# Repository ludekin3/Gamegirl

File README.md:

# Gamegirl

The most portable way to play LÖVE, PICO-8, Scratch or your favorite emulated games. Powered by RetroArch!

# Table of Contents

* [Description](#description)
* [Components](#components)
* [Build your own!](#build-your-own)
* [Setup](#setup)
* [Team](#team)
* [License](#license)

# Description
We develop a very small, affordable and portable gaming console with a 320x240 display at 120 FPS run by a Raspberry Pi Zero.
Gamegirl runs on the Lakka distribution powered by RetroArch because of its speed, fast power-on, instant power-off and its potential to run many retro and hipster-retro games (LÖVE, PICO-8, Scratch and emulators).

[**Join us on our Discord Chat Channel!**](https://discord.gg/TZ7MZEu)

<p align="center">
    
</p>

**Project Goals:**
* Hardware accelerated display
* Custom software (Lakka / RetroArch)
* High quality case and buttons
* Small form factor

# Components
* 1 x Gamegirl custom PCB (audio, power, etc.)
* 1 × Raspberry Pi Zero
* 1 × 2.4" TFT display 320x240 (RGB 565 @ 120 FPS)
* 10 × soft rubber dome buttons
* 2 x metal dome buttons
* 1 × 15-16mm speaker
* 1 × 800+ mAh battery

# Build your own!

## Prototype v0.2 (_released_)
**v0.2** is the current development platform with multiple working prototypes in the field. It works but it's not perfect, yet!

### Gamegirl v0.2 - Schematic
* [Gamegirl_v0.2_Schematic.pdf](./Electronics%20v0.2/Gamegirl_v0.2_Schematic.pdf)

### Gamegirl v0.2 - Bill Of Materials (BOM)
* [Octopart - Gamegirl v0.2 BOM](https://octopart.com/bom-tool/0X5BikOH)

#### Minimal assembly variant
In this assembly variant you will get a working prototype without battery/charging and audio functionality. You can use it only while the Raspberry Pi Zero is connected to a USB power supply!
* [Gamegirl v0.2 BOM - minimal assembly variant](./Electronics%20v0.2/Gamegirl_v0.2_BOM_minimal.pdf)

#### Full assembly variant
This assembly variant requires some circuit modifications to get audio output!
* [Gamegirl v0.2 BOM - full assembly variant](./Electronics%20v0.2/Gamegirl_v0.2_BOM.pdf)

### Gamegirl Case v0.2
A 3D printable case design is currently in work.

## Prototype v0.2.1 (Awaiting Prototype board)
**v0.2.1** incorporates multiple improvements and fixes over v0.2. If you do not have a v0.2, you should wait for this!

**Improvements over v0.2:**
* Friendlier hand solderable layout (All component footprints have been expanded for soldering without a heatgun)
* Fixed mono audio circuit (better pre and post filtering)
* Fixed backlight function
* Button placement and labeling to reflect standard Nintendo layout
* MCP23S17 GPIO Expander replaced Charlieplexed buttons
* Labeled most 
* Ability to add common inexpensive WiFi adpater directly to the board (depreciated due to Zero W)
* Replaced battery charger and 5v booster ICs with a 3-in-1 IC, ETA9740
** Rpi Zero will run directly from battery (Rpi stability has been tested down to 3.0V)
** Increased charging current from 500mA to 2A or 3A
** 5V Boost will operate in USB-OTG mode for accessories
* Added dedicated charging micro USB port (Rpi ports will be covered)
* Added multiple power decoupling capacitors for better power filtering
* Added Safe Soft-Shutdown circuit
* Replaced latching switch with momentary switch
* (Optional) Low Battery shutdown
* (Optional) Low Noise LDO for audio amp (Must cut 3.3v trace when using)

### Gamegirl v0.2.1 - Bill Of Materials (BOM)
[BOM](./Electronics%20v0.2.1/Gamegirl_v0.2.1_BOM.csv)

### Gamegirl Case v0.2.1
(work in progress)

# Setup
## Install the latest Lakka image on an SD Card

**Gamegirl Raspberry Pi Zero images:**
* [Nightly Builds](http://sources.lakka.tv/nightly/Gamegirl.arm-8.0/)
* [Build r21684 (November 29, 2016)](http://static.kivutar.me/Lakka-Gamegirl.arm-devel-20161129161645-r21684-g895e996.img.gz)
* [Build r21570 (August 23, 2016)](http://static.kivutar.me/Lakka-Gamegirl.arm-devel-20160823060147-r21570-g1cacbe2.img.gz)

**Instructions:**
* [How to write a image to an SD card on Windows & Mac OS](http://trendblog.net/install-raspbian-sd-card-os-x-windows/)

## First boot
As of nightly build 20170110005640-r25097, the system will take longer to boot as it is expanding the SD card partition and running other first boot operations. Subsequent boots will be faster.

## Installing your games
How-to [on lakka.tv](http://www.lakka.tv/get/linux/rpi/install/first-boot/games/)

# Team
|  |  |  
| --- | --- | --- |
| [David Perrenoud](https://github.com/davidperrenoud) | [Jean-André Santoni](http://www.kivutar.me/) - [Github](https://github.com/Kivutar) | [Rodney Yates](https://github.com/zybeon)

- [Jean-André] from France is the software guy of this project. He is the main Lakka developer and a top 5 RetroArch contributor.
- [David] from Switzerland is the hardware guy.
- [Rodney] from US is the PCB designer.

## Contributing
[Join us on our Discord Chat Channel!](https://discord.gg/TZ7MZEu)

### Project Task Tracker
[Trello page](https://trello.com/b/wslfYlVv/gamegirl)

#License

All hardware is covered under [OSHW](https://www.oshwa.org/definition/).

All software is covered under [GNU-GPL 3.0](https://opensource.org/licenses/GPL-3.0).

Permission is hereby granted, free of charge, to any person obtaining a copy of this software and associated documentation files (the "Software"), to deal in the Software without restriction, including without limitation the rights to use, copy, modify, merge, publish, distribute, sublicense, and/or sell copies of the Software, and to permit persons to whom the Software is furnished to do so, subject to the following conditions:  The above copyright notice and this permission notice shall be included in all copies or substantial portions of the Software. THE SOFTWARE IS PROVIDED "AS IS", WITHOUT WARRANTY OF ANY KIND, EXPRESS OR IMPLIED, INCLUDING BUT NOT LIMITED TO THE WARRANTIES OF MERCHANTABILITY, FITNESS FOR A PARTICULAR PURPOSE AND NONINFRINGEMENT. IN NO EVENT SHALL THE AUTHORS OR COPYRIGHT HOLDERS BE LIABLE FOR ANY CLAIM, DAMAGES OR OTHER LIABILITY, WHETHER IN AN ACTION OF CONTRACT, TORT OR OTHERWISE, ARISING FROM, OUT OF OR IN CONNECTION WITH THE SOFTWARE OR THE USE OR OTHER DEALINGS IN THE SOFTWARE."

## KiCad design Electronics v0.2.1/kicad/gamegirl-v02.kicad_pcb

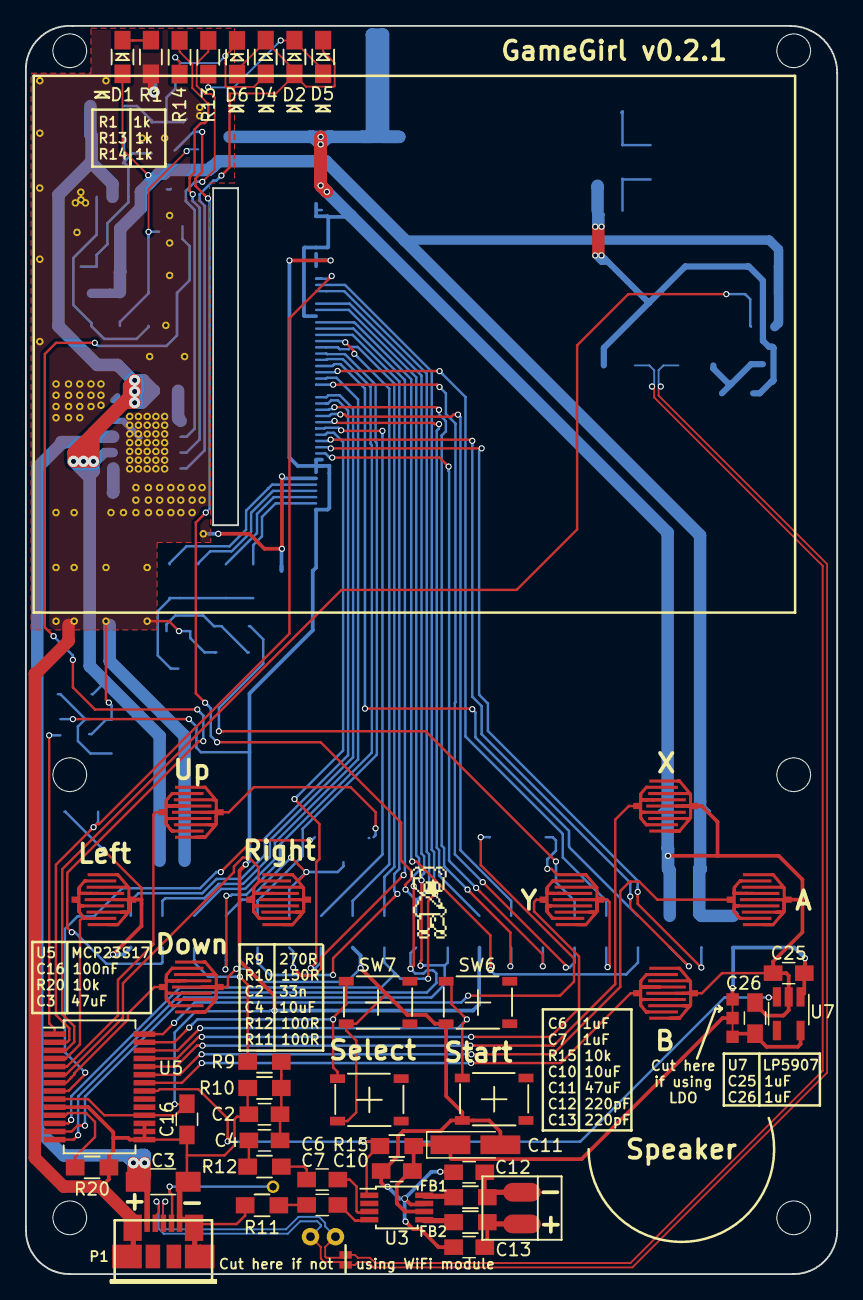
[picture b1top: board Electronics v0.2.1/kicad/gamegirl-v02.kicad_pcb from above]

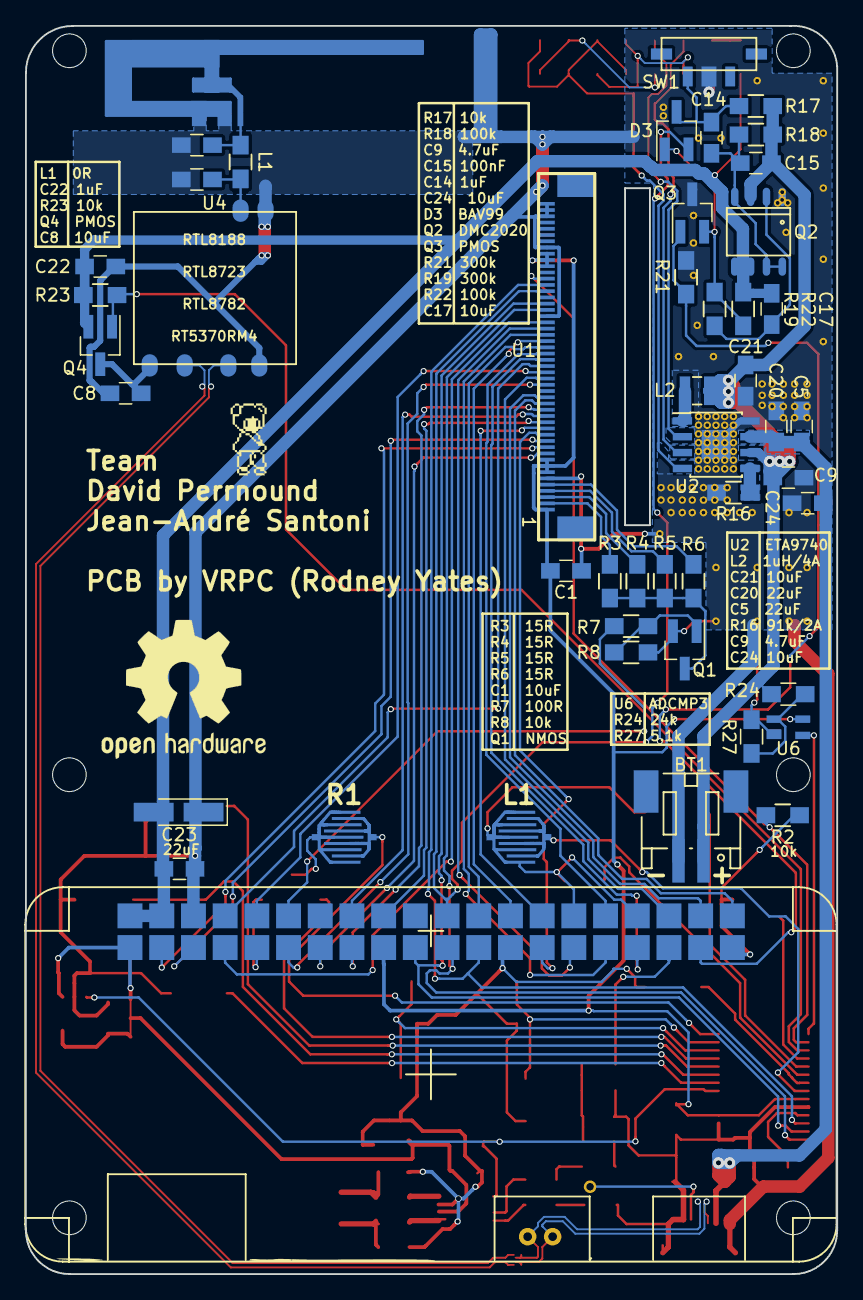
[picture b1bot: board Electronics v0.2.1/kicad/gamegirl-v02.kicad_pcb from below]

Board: 2 copper layers, 65.0 x 100.0 mm, 95 parts (48 on the bottom side), 90 nets.

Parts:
AE1: PCB Antenna DN0007; ANTENNA_TI_AN0007_2.4GHz
BT1: Battery; JST_PH_S2B-PH-SM4-TB_02x2.00mm_Extended
C1, C4, C8, C10, C17, C21, C24: 10uF; C_0805_HandSoldering
C2: 33nF; C_0805_HandSoldering
C3: 47uF; C_1206_HandSoldering
C5, C20, C23: 22uF; C_0805_HandSoldering
C6, C7, C14, C22, C25, C26: 1uF; C_0805_HandSoldering
C9: 4.7uF; C_0805_HandSoldering
C11: 47uF; CP_Tantalum_Case-A_EIA-3216-18_Hand
C12, C13: 220pF; C_0805_HandSoldering
C15, C16: 100nF; C_0805_HandSoldering
C18, C19: NC; C_0805_HandSoldering
D1, D2, D4, D5, D6: LED_Green; D_0805_HandSoldering
D3: D_Schottky_x2_KCom_AAK; SOT-23_Handsoldering
FB1, FB2: MPZ2012S101A; R_0805_HandSoldering
JP1: Jumper_NC_Dual; NetTie-II_SMD-Connected
JP2: Jumper_NC_Small; NetTie-I_Connected_SMD
JP3: Jumper_USB_90ohm; NetTie-USB_90ohm
L1: 0R; R_0805_HandSoldering
L2: 1uH; Inductor_Wurth_MAPI-2512
P1: Molex 47346-0001; conn_usb_B_micro_smd
P2: PI-ZERO; raspberry-zero
Q1: Q_NMOS_DGS; SOT-23_Handsoldering
Q2: DMC2020; SO-8
Q3, Q4: Q_PMOS_DGS; SOT-23_Handsoldering
R1, R13, R14: 1k; R_0805_HandSoldering
R2, R8, R15, R17, R20, R23: 10k; R_0805_HandSoldering
R3, R4, R5, R6: 15R; R_0805_HandSoldering
R7, R11, R12: 100; R_0805_HandSoldering
R9: 270; R_0805_HandSoldering
R10: 150; R_0805_HandSoldering
R16: 91k; R_0805_HandSoldering
R18, R22: 100k; R_0805_HandSoldering
R19, R21: 300k; R_0805_HandSoldering
R24: 24k; R_0805_HandSoldering
R27: 5.1k; R_0805_HandSoldering
SP1: SPEAKER; Speaker-Pinout
SW1: JSX08001SAQNL; JSX_Series_minature_switch
SW2: UP; round_rubber_pad_4.7mm
SW3: DOWN; round_rubber_pad_4.7mm
SW4: RIGHT; round_rubber_pad_4.7mm
SW5: LEFT; round_rubber_pad_4.7mm
SW6, SW6#2: STA; SW_DOME_4x4.6_SMD
SW7, SW7#2: SEL; SW_DOME_4x4.6_SMD
SW8: L1; round_rubber_pad_4.7mm
SW9: R1; round_rubber_pad_4.7mm
SW10: Y; round_rubber_pad_4.7mm
SW11: X; round_rubber_pad_4.7mm
SW12: B; round_rubber_pad_4.7mm
SW13: A; round_rubber_pad_4.7mm
U1: ER-TFT024-3; ER-CON50HT-1
U2: ETA9740; SOIC-8-1EP_3.9x4.9mm_Pitch1.27mm
U3: PAM8302A; MSOP-8_3x3mm_Pitch0.65mm
U4: RTL8188; RTL8188_WiFi_USB_module
U5: MCP23S17; SSOP-28_5.3x10.2mm_Pitch0.65mm
U6: ADCMP354; SC-82_handsolderable
U7: LP5907; SOT-23-5_HandSoldering

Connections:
+3V3: C1.2, C16.1, C25.2, JP1.3, P2.1, P2.17, U1.1, U1.7, U1.8, U1.9, U1.40, U1.41, U1.42, U5.9, U5.18, U6.4, U7.1
/AMP_SD: R15.1, U3.1, U5.21, U7.3
/AUDIO: P2.35, R9.2
/BL: P2.12, R7.2
/BLU3: P2.7, U1.31
/BLU4: P2.29, U1.30
/BLU5: P2.31, U1.29
/BLU6: P2.26, U1.28
/BLU7: P2.24, U1.27
/BTN_A: SW13.1, U5.23
/BTN_B: SW12.1, U5.22
/BTN_SEL: SW7.1, SW7#2.1, U5.27
/BTN_STA: SW6.1, SW6#2.1, U5.26
/BTN_X: SW11.1, U5.24
/BTN_Y: SW10.1, U5.25
/CLOCK: P2.27, U1.13
/DC: JP2.1, P2.22, U1.36
/DEN: P2.28, U1.14
/DIR_D: SW3.1, U5.7
/DIR_L: SW5.1, U5.4
/DIR_R: SW4.1, U5.6
/DIR_U: SW2.1, U5.5
/GRE2: P2.32, U1.26
/GRE3: P2.33, U1.25
/GRE4: P2.8, U1.24
/GRE5: P2.10, U1.23
/GRE6: P2.36, U1.22
/GRE7: P2.11, U1.21
/HSYNC: P2.5, U1.12
/KILL: P2.37, Q3.1, R21.2
/LBO: U5.1, U6.3
/LED1: R3.2, U1.2
/LED2: R4.2, U1.3
/LED3: R5.2, U1.4
/LED4: R6.2, U1.5
/MISO: P2.21, U1.33, U5.14
/MOSI: P2.19, U1.34, U5.13
/RED3: P2.38, U1.19
/RED4: P2.40, U1.18
/RED5: P2.15, U1.17
/RED6: P2.16, U1.16
/RED7: P2.18, U1.15
/RST: P2.13, U1.10
/SCK: P2.23, U1.37, U5.12
/SHDN: D3.2, JP2.2
/SS1: R2.2, U1.38, U5.2
/TGR_L1: SW8.1, U5.8
/TGR_R1: SW9.1, U5.28
/USB_D+: JP3.2, P1.3, P2.42
/USB_D-: JP3.1, P1.2, P2.41
/USB_ID: P1.4, P2.43
/VSYNC: P2.3, U1.11
/WiFi_D+: JP3.4, U4.3
/WiFi_D-: JP3.3, U4.2
/WiFi_EN: Q4.1, R23.1, U5.3
GND: AE1.2, BT1.2, C1.1, C2.2, C3.2, C5.2, C8.1, C9.2, C10.2, C11.2, C12.1, C13.1, C16.2, C18.1, C19.1, C20.2, C21.1, C22.1, C23.1, C24.2, C25.1, C26.2, P1.5, P1.6, P2.6, P2.9, P2.25, P2.30, P2.34, P2.39, Q1.2, Q2.1, Q3.3, R1.2, R2.1, R8.2, R10.1, R11.1, R16.2, R20.1, R21.1, R27.2, SW1.2, SW2.2, SW3.2, SW4.2, SW5.2, SW6.2, SW6#2.2, SW7.2, SW7#2.2, SW8.2, SW9.2, SW10.2, SW11.2, SW12.2, SW13.2, U1.6, U1.20, U1.32, U1.43, U1.48, U1.49, U1.50, U2.8, U2.9, U3.7, U4.4, U4.5, U5.10, U5.15, U5.16, U5.17, U6.2, U7.2
unnamed: AE1.1, C19.2, L1.2
unnamed: C2.1, C4.2, R9.1, R10.2
unnamed: C4.1, R12.2
unnamed: C6.1, U3.3
unnamed: C6.2, R12.1
unnamed: C7.1, U3.4
unnamed: C7.2, R11.2
unnamed: C8.2, Q4.3, U4.1
unnamed: C12.2, FB1.2, SP1.1
unnamed: C13.2, FB2.2, SP1.2
unnamed: C14.1, C15.2, Q2.4, Q2.7, Q2.8, R18.1
unnamed: C17.2, Q2.2, R19.2
unnamed: C18.2, L1.1, U4.6
unnamed: C26.1, JP1.1, U7.5
unnamed: D1.1, R1.1
unnamed: D2.1, D5.2, R13.1
unnamed: D2.2, D4.1, D5.1, D6.2, U2.4
unnamed: D3.1, Q3.2, R19.1, R22.1
unnamed: D4.2, D6.1, R14.1
unnamed: FB1.1, U3.8
unnamed: FB2.1, U3.5
unnamed: L2.1, U2.1
unnamed: Q1.1, R7.1, R8.1
unnamed: Q1.3, R3.1, R4.1, R5.1, R6.1
unnamed: R13.2, U2.2
unnamed: R14.2, U2.3
unnamed: R16.1, U2.5
unnamed: R20.2, U5.11
unnamed: R24.2, R27.1, U6.1
SW: C14.2, D3.3, R17.1, SW1.3
VAMP: C10.1, C11.1, JP1.2, R15.2, U3.6
VBAT: BT1.1, C9.1, C15.1, C21.2, L2.2, Q2.3, R17.2, R18.2, R24.1, U2.6
VBUS: C17.1, C22.2, C23.2, D1.2, P2.2, P2.4, Q2.5, Q2.6, Q4.2, R22.2, R23.2
VUSB: C3.1, C5.1, C20.1, C24.1, P1.1, U2.7

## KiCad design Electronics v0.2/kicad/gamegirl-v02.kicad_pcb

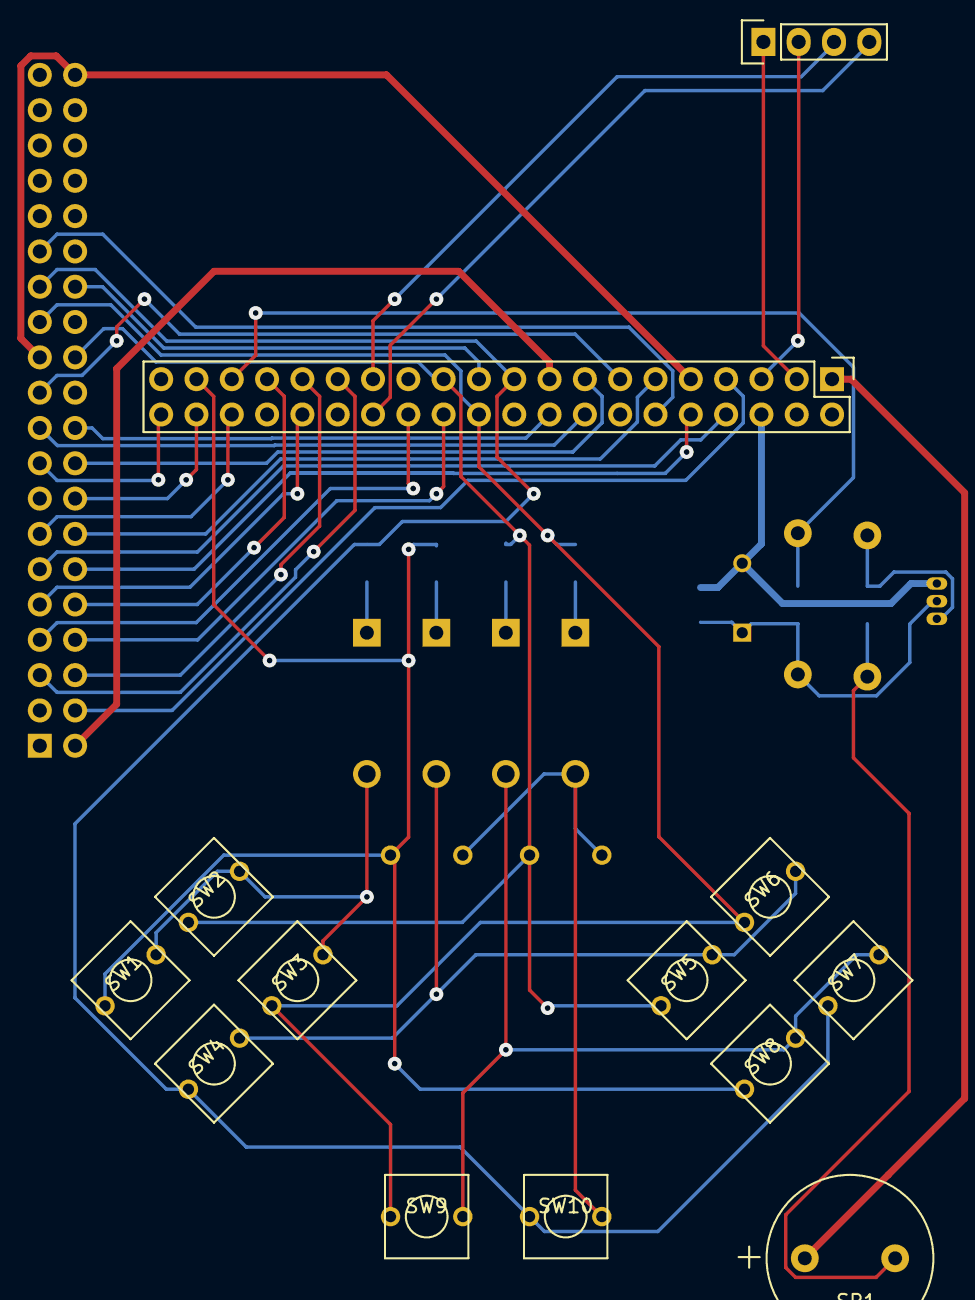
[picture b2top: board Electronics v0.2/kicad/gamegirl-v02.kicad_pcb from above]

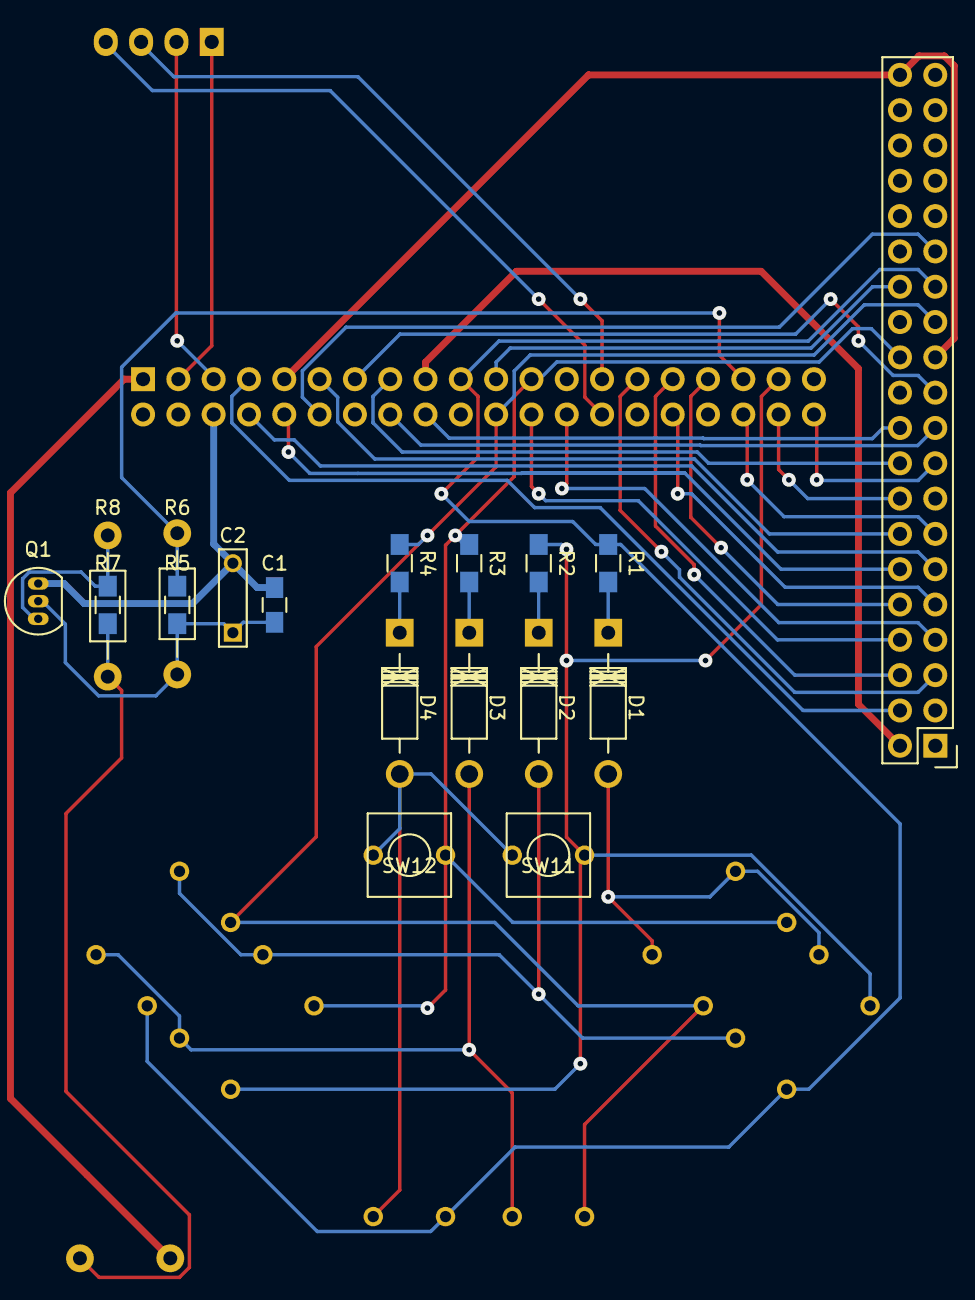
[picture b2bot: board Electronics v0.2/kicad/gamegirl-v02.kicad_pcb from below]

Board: 2 copper layers, 31 parts (18 on the bottom side), 42 nets.

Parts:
C1: 100nF; C_0805_HandSoldering
C2: 100nF; C_Rect_L7_W2_P5
D1, D2, D3, D4: D; Diode_DO-41_SOD81_Horizontal_RM10
P1, P3: CONN_02X20; Pin_Header_Straight_2x20
P2: CONN_01X04; Pin_Header_Straight_1x04
Q1: Q_NMOS_DGS; TO-92_Inline_Narrow_Oval
R1, R2, R3, R4: 1k; R_0805_HandSoldering
R5: 680; R_0805_HandSoldering
R6: 680; Resistor_Horizontal_RM10mm
R7: 0; R_0805_HandSoldering
R8: 0; Resistor_Horizontal_RM10mm
SP1: SPEAKER; Buzzer_12x6.5RM6.5
SW1, SW2, SW3, SW4, SW5, SW6, SW7, SW8, SW9, SW10, SW11, SW12: SW_PUSH; SW_PUSH_8x8_DIP

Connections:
+3V3: P1.2, P3.1, P3.17, SP1.1
/5V: P3.2, P3.4
//RESET_NC: P1.21, P3.13
/AUDIO: P3.35, R5.2, R6.2
/BL: P1.29, P3.12
/BLU3: P1.4, P3.7
/BLU4: P1.5, P3.29
/BLU5: P1.6, P3.31
/BLU6: P1.7, P3.26
/BLU7: P1.8, P3.24
/BTN1: P1.27, P3.19, R1.2, SW4.1, SW7.1, SW10.1
/BTN2: P3.37, R2.2, SW1.1, SW8.1, SW11.1
/BTN3: P1.24, P3.23, R3.2, SW2.1, SW5.1, SW12.1
/BTN4: P1.25, P3.22, R4.2, SW3.1, SW6.1, SW9.1
/CLOCK: P2.3, P3.27
/DB6: P1.9, P3.32
/DB7: P1.10, P3.33
/DB8: P1.11, P3.8
/DB9: P1.12, P3.10
/DB10: P1.13, P3.36
/DB11: P1.14, P3.11
/DB13: P1.16, P3.38
/DB14: P1.17, P3.40
/DB15: P1.18, P3.15
/DB16: P1.19, P3.16
/DB17: P1.20, P3.18
/DEN: P2.4, P3.28
/GPIO2: P2.1, P3.3
/GPIO3: P2.2, P3.5
/GPIO9: P1.28, P3.21
GND: C1.2, C2.2, P1.1, P1.23, P1.40, P3.6, P3.9, P3.14, P3.20, P3.25, P3.30, P3.34, P3.39, Q1.3
unnamed: C1.1, C2.1, Q1.2, R5.1, R6.1
unnamed: D1.1, R1.1
unnamed: D1.2, SW1.2, SW2.2, SW3.2
unnamed: D2.1, R2.1
unnamed: D2.2, SW4.2, SW5.2, SW6.2
unnamed: D3.1, R3.1
unnamed: D3.2, SW7.2, SW8.2, SW9.2
unnamed: D4.1, R4.1
unnamed: D4.2, SW10.2, SW11.2, SW12.2
unnamed: Q1.1, R7.2, R8.1
unnamed: R7.1, R8.2, SP1.2

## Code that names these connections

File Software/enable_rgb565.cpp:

#include <wiringPi.h>
#include <wiringPiSPI.h>

using namespace std;

#define ILI9340_SWRESET 0x01
#define ILI9340_SLPOUT  0x11
#define ILI9340_GAMMASET 0x26
#define ILI9340_DISPOFF 0x28
#define ILI9340_DISPON  0x29
#define ILI9340_MADCTL  0x36
#define ILI9340_PIXFMT  0x3A

#define ILI9340_PWCTR1  0xC0
#define ILI9340_PWCTR2  0xC1
#define ILI9340_VMCTR1  0xC5
#define ILI9340_VMCTR2  0xC7

#define ILI9340_GMCTRP1 0xE0
#define ILI9340_GMCTRN1 0xE1

#define ILI9340_CASET   0x2A
#define ILI9340_PASET   0x2B
#define ILI9340_RAMWR   0x2C

int _clock = 0; // GPIO 0
int _den = 1; // GPIO 1
int _vsync = 2; // GPIO 2
int _hsync = 3; // GPIO 3
int _blu3 = 4; // GPIO 4
int _blu4 = 5; // GPIO 5
int _blu5 = 6; // GPIO 6
int _blu6 = 25; // GPIO 7
int _blu7 = 26; // GPIO 8
int _gre2 = 12; // GPIO 12
int _gre3 = 13; // GPIO 13
int _gre4 = 14; // GPIO 14
int _gre5 = 15; // GPIO 15
int _gre6 = 16; // GPIO 16
int _gre7 = 17; // GPIO 17
int _red3 = 20; // GPIO 20
int _red4 = 21; // GPIO 21
int _red5 = 22; // GPIO 22
int _red6 = 23; // GPIO 23
int _red7 = 24; // GPIO 24

int _dc = 25; // GPIO 25    | LCD DC
int _rst = 27; // GPIO 27   | LCD Reset
int _mosi = 10; // GPIO 10  | SPI MOSI
int _miso = 9; // GPIO 9    | SPI MISO
int _sclk = 11; // GPIO 11  | SPI Clock
int _lcd_cs = 26; //GPIO26  | LCD SPI Chip Select
int _mcp_cs = 18; // GPIO 18| MCP23S17 Chip Select
int _audio = 19; //         | RPi PWM Audio

int _channel = 1;
int _speed = 80000000;//80000000;//500000;//80000000;

void spiwritearray(unsigned char c[], int length) {
	wiringPiSPIDataRW(_channel, c, length);
}

void spiwrite(unsigned char c) {
	wiringPiSPIDataRW(_channel, &c, 1);
}

void writecommand(int c) {
  digitalWrite(_dc, LOW);
//  digitalWrite(_sclk, LOW);
  
  spiwrite(c);
}

void writedata(int c) {
  digitalWrite(_dc, HIGH);
//  digitalWrite(_sclk, LOW);
  
  spiwrite(c);
}

void begin() {
  pinMode(_rst, OUTPUT);
  digitalWrite(_rst, LOW);
  
  pinMode(_dc, OUTPUT);

  // Initialise SPI
  pinMode(_lcd_cs, OUTPUT);
  pinMode(_mcp_cs, OUTPUT);
  digitalWrite(_lcd_cs, LOW);
  digitalWrite(_mcp_cs, HIGH);
  wiringPiSPISetup(_channel, _speed);
  
  // Initialise DPI pins
  const int ALT2 = 0b110;
  pinModeAlt(_clock, ALT2);
  pinModeAlt(_den, ALT2);
  pinModeAlt(_vsync, ALT2);
  pinModeAlt(_hsync, ALT2);
  pinModeAlt(_blu3, ALT2);
  pinModeAlt(_blu4, ALT2);
  pinModeAlt(_blu5, ALT2);
  pinModeAlt(_blu6, ALT2);
  pinModeAlt(_blu7, ALT2);
  pinModeAlt(_gre2, ALT2);
  pinModeAlt(_gre3, ALT2);
  pinModeAlt(_gre4, ALT2);
  pinModeAlt(_gre5, ALT2);
  pinModeAlt(_gre6, ALT2);
  pinModeAlt(_gre7, ALT2);
  pinModeAlt(_red3, ALT2);
  pinModeAlt(_red4, ALT2);
  pinModeAlt(_red5, ALT2);
  pinModeAlt(_red6, ALT2);
  pinModeAlt(_red7, ALT2);
  
  // toggle RST low to reset
  if (_rst > 0) {
    digitalWrite(_rst, HIGH);
    delay(5);
    digitalWrite(_rst, LOW);
    delay(20);
    digitalWrite(_rst, HIGH);
    delay(150);
  }
  
  writecommand(ILI9340_SWRESET);
  delay(1);
  
  writecommand(ILI9340_DISPOFF);
  
  /*
  writecommand(0xCA);
  writedata(0xC3);
  writedata(0x08);
  writedata(0x50);
  */
  
  writecommand(0xEF);
  writedata(0x03);
  writedata(0x80);
  writedata(0x02);
  
  writecommand(0xCF); // LCD_POWERB
  writedata(0x00);
  writedata(0XC1);
  writedata(0X30);
  
  writecommand(0xED); // LCD_POWER_SEQ
  writedata(0x64);
  writedata(0x03);
  writedata(0X12);
  writedata(0X81);
  
  writecommand(0xE8); // LCD_DTCA
  writedata(0x85);
  writedata(0x00);
  writedata(0x78);
  
  writecommand(0xCB); // LCD_POWERA
  writedata(0x39);
  writedata(0x2C);
  writedata(0x00);
  writedata(0x34);
  writedata(0x02);
  
  writecommand(0xF7); // LCD_PRC
  writedata(0x20);
  
  writecommand(0xEA); // LCD_DTCB
  writedata(0x00);
  writedata(0x00);
  
  /*
  writecommand(0xB1); // LCD_FRC // Frame Rate Control
  writedata(0x00);
  writedata(0b00010000); // 0x1B=70 FPS
  */
  // LCD_DFC
  
  writecommand(ILI9340_PWCTR1);    //Power control // 0xC0
  writedata(0x23);
  
  writecommand(ILI9340_PWCTR2);    //Power control // 0xC1
  writedata(0x10);
  
  writecommand(ILI9340_VMCTR1);    //VCM control // 0xC5
  writedata(0x3e); // 0x31?
  writedata(0x28); // 0x3C?
  
  writecommand(ILI9340_VMCTR2);    //VCM control2 // 0xC7
  writedata(0x86); // 0xC0? 0x86?
  
  writecommand(ILI9340_MADCTL);    // Memory Access Control  // 0x36
  writedata(0b01001000); // MY=1, MX=0, MV=1 (0b01000000), BGR=1 (0b01001000)
  
  writecommand(ILI9340_PIXFMT); // 0x3A
  writedata(0x55); // 16-bit: DPI=101 // 18-bit=0x66
  
  writecommand(0xF2); // 3Gamma Function Disable
  writedata(0x02);
  
  writecommand(0xB0); // RGB Interface Signal Control
  writedata(0b11000011); // memory=1 RCM=10, 0, VSPL=0 (low level sync clock), HSPL=0, DPL=1 (dotclock fetched at rising time), EPL=0 (high enable)
  // 0xC2? DEFAULT: 0x40, 0b01000000
  
  writecommand(0xB6); // LCD_DFC // Display Function Control
  writedata(0x0A);
  writedata(0b10000010); // =0x82
  writedata(0x27);
  writedata(0x08); // PCDIV = 4
  
  writecommand(0x2A); // column set
  writedata(0x00);
  writedata(0x00);
  writedata(0x00);
  writedata(0xEF);
  
  writecommand(0x2B); // Page set
  writedata(0x00);
  writedata(0x00);
  writedata(0x01);
  writedata(0x3F);
  
  writecommand(0xF6); // Interface Control
  writedata(0x01);
  writedata(0b00000000); // EPF=11
  writedata(0b00001010); // 16-bit RGB=0b00000110, DM=01, RM=1, RIM=0
  
  writecommand(0x2C); // GRAM register
  delay(1);
  
  writecommand(ILI9340_GAMMASET);    //Gamma curve selected // 0x26
  writedata(0x01);
  
  writecommand(ILI9340_GMCTRP1);    //Set Gamma // 0xE0
  writedata(0x0F);
  writedata(0x31);
  writedata(0x2B);
  writedata(0x0C);
  writedata(0x0E);
  writedata(0x08);
  writedata(0x4E);
  writedata(0xF1);
  writedata(0x37);
  writedata(0x07);
  writedata(0x10);
  writedata(0x03);
  writedata(0x0E);
  writedata(0x09);
  writedata(0x00);
  
  writecommand(ILI9340_GMCTRN1);    //Set Gamma // 0xE1
  writedata(0x00);
  writedata(0x0E);
  writedata(0x14);
  writedata(0x03);
  writedata(0x11);
  writedata(0x07);
  writedata(0x31);
  writedata(0xC1);
  writedata(0x48);
  writedata(0x08);
  writedata(0x0F);
  writedata(0x0C);
  writedata(0x31);
  writedata(0x36);
  writedata(0x0F);
  
  writecommand(0xB5); // Blanking Porch Control
  writedata(0x04); // VFP
  writedata(0x02); // VBP
  writedata(0x0A); // HFP
  writedata(0x14); // 0x14? 0x16? HBP
  
  writecommand(0x2D); // Color Set LUT
  for (unsigned char i = 0; i < 32; i++) {
    writedata(63*i/31);
  }
  for (unsigned char i = 0; i < 64; i++) {
    writedata(i);
  }
  for (unsigned char i = 0; i < 32; i++) {
    writedata(63*i/31);
  }
  
  writecommand(ILI9340_SLPOUT);    //Exit Sleep
  delay(120);
  writecommand(ILI9340_DISPON);    //Display on
  delay(120);
  writecommand(0x2C); // memory write
  
  // Initialise backlight
//  pinMode(_backlight, PWM_OUTPUT);
//  pwmWrite(_backlight, 1023);
  //pinMode(_backlight, OUTPUT);
  //digitalWrite(_backlight, HIGH);
  
  /*
  pwmSetMode  (PWM_MODE_BAL) ;	// Pi default mode
  pwmSetClock (32) ;		// 19.2 / 32 = 600KHz - Also starts the PWM
  */
  
  /*
  *(pwm + PWM_CONTROL) = PWM0_ENABLE | PWM1_ENABLE ;
  *(pwm + PWM0_RANGE) = 1024;
  
  uint32_t pwm_control = *(pwm + PWM_CONTROL); // preserve PWM_CONTROL
  *(pwm + PWM_CONTROL) = 0; // Stop PWM
  
  
  pwmWrite(_backlight, 1023);
  */
  
  // Initialise audio
//  const int ALT5 = 0b010;
//  pinModeAlt(_audio, ALT5);
	
  // Turn off LCD SPI bus
  digitalWrite(_lcd_cs, HIGH);
}

int main() {
	wiringPiSetupGpio();
	
	begin();
}

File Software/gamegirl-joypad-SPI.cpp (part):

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
using namespace std;

//int _SHDN = 25; // GPIO25 - Power switch
int _mcp_cs = 18; // GPIO18 - MCP23S17 SPI Chip Select
int _lcd_cs = 26; // GPIO26 - LCD SPI Chip Select

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  }

  //Power switch setup
  pinMode(_SHDN, INPUT);
  pullUpDnControl(_SHDN,PUD_UP);
  
  //Sets Chip Select pin of LCD high disabling the SPI connection
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  //pullUpDnControl(_SS1,PUD_UP);

  //Enables WiFi by default
  pinMode(_WiFi_EN,OUTPUT);
  digitalWrite(_WiFi_EN,1);//Enables power to WiFi module
  system("connmanctl enable wifi");//Enables WiFi connections
    
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  int l1_button, l1_button_old         = 1;
  int r1_button, r1_button_old         = 1;
  int powerswitch                      = 1;
  int LBO                              = 1;
  int toggle_timeout                   = 0; //Toggle timeout for toggling WiFi or Amp
  int shdn_delay                       = 0; //Delay (debounce) for shutdown switch
  int LBO_delay                        = 0; //Delay  for LBO

  while (1) {
    // Read GPIO
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
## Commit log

2016-05-05 Issues moved to Trello
2016-12-19 Adding prototype v0.2 schematic
    v0.2 schematic
    Gamegirl_Controller.cfg for v0.2
2016-12-21 Updated links
    Updated a few links
    Added youtube video
    Added links to lakka image build files
    Added a few extra instructions for setting up SD card
2017-01-01 GameGirl -> Gamegirl
2017-01-01 GameGirl -> Gamegirl (2)
2017-01-01 Typos
2017-01-01 media -> Media
2017-01-01 Create Electronics directory
2017-01-01 Create Software directory
2017-01-01 Add v0.1 schematic
2017-01-01 Create Mechanical directory
2017-01-02 First boot
2017-01-02 Final v0.2 schematic
2017-01-13 reflecting changes in latest nightly build
2017-01-14 Added different prototype versions
    * v0.2, v0.2.1, v0.3 descriptions added
    * Complete readme revisioned
2017-01-14 repo relative links
2017-01-18 Added BOM, updated README
2017-01-18 Fixed README
2017-01-24 Octopart BOM; fixed PDF links
2017-02-17 Updated V0.2.1 prototype image
2017-02-17 changed description of v0.2.1
2017-03-08 Updated v0.2.1 image
2017-03-08 Added license information
2017-03-08 updated TOC
2017-03-20 Corrected images not showing
2017-03-20 Final v0.2.1
2017-03-20 v0.2.1 BOM
2017-03-20 Added v0.2.1 BOM link
2017-04-04 gamegirl v0.2.1 schematic
2017-06-01 Screen initialization of ili9341
    Initializes ili9341 LCD's into DPI mode over SPI and sets Raspberry Pi into DPI 16-bit (RGB565) mode.
2017-06-23 Changed SPI channel, added PWR switch delay
    Changed SPI channel to match the one used in "enable_rgb565.cpp"
    Updated toggling of WiFi and AMP for more reliablility
    Added a 0.5s delay on Power switch and low battery input for debouncing and reduce unintended shutdown.
2017-06-23 Added commandline toggling of wifi connection
    Enables or disables wifi using "connmanctl enable/disable wifi"
2017-12-26 Add Kicad files
2017-12-26 Fix README links
2018-01-27 testing
2018-01-28 temp test for compiling
2018-02-09 Added use of SPI chip select pins
    Add GPIO26 to be LCD chip select pin
    Changed GPIO18 to be MCP23S17 chip select pin
    Ensured the MCP is not listening and talking on the SPI bus while the LCD is initializing
2018-02-10 Added use of SPI chip select pins
2020-03-14 Create sym-lib-table
2020-03-14 Create gamegirl-v02.sch-bak

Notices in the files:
README.md:
GNU GPLv3 Logo
